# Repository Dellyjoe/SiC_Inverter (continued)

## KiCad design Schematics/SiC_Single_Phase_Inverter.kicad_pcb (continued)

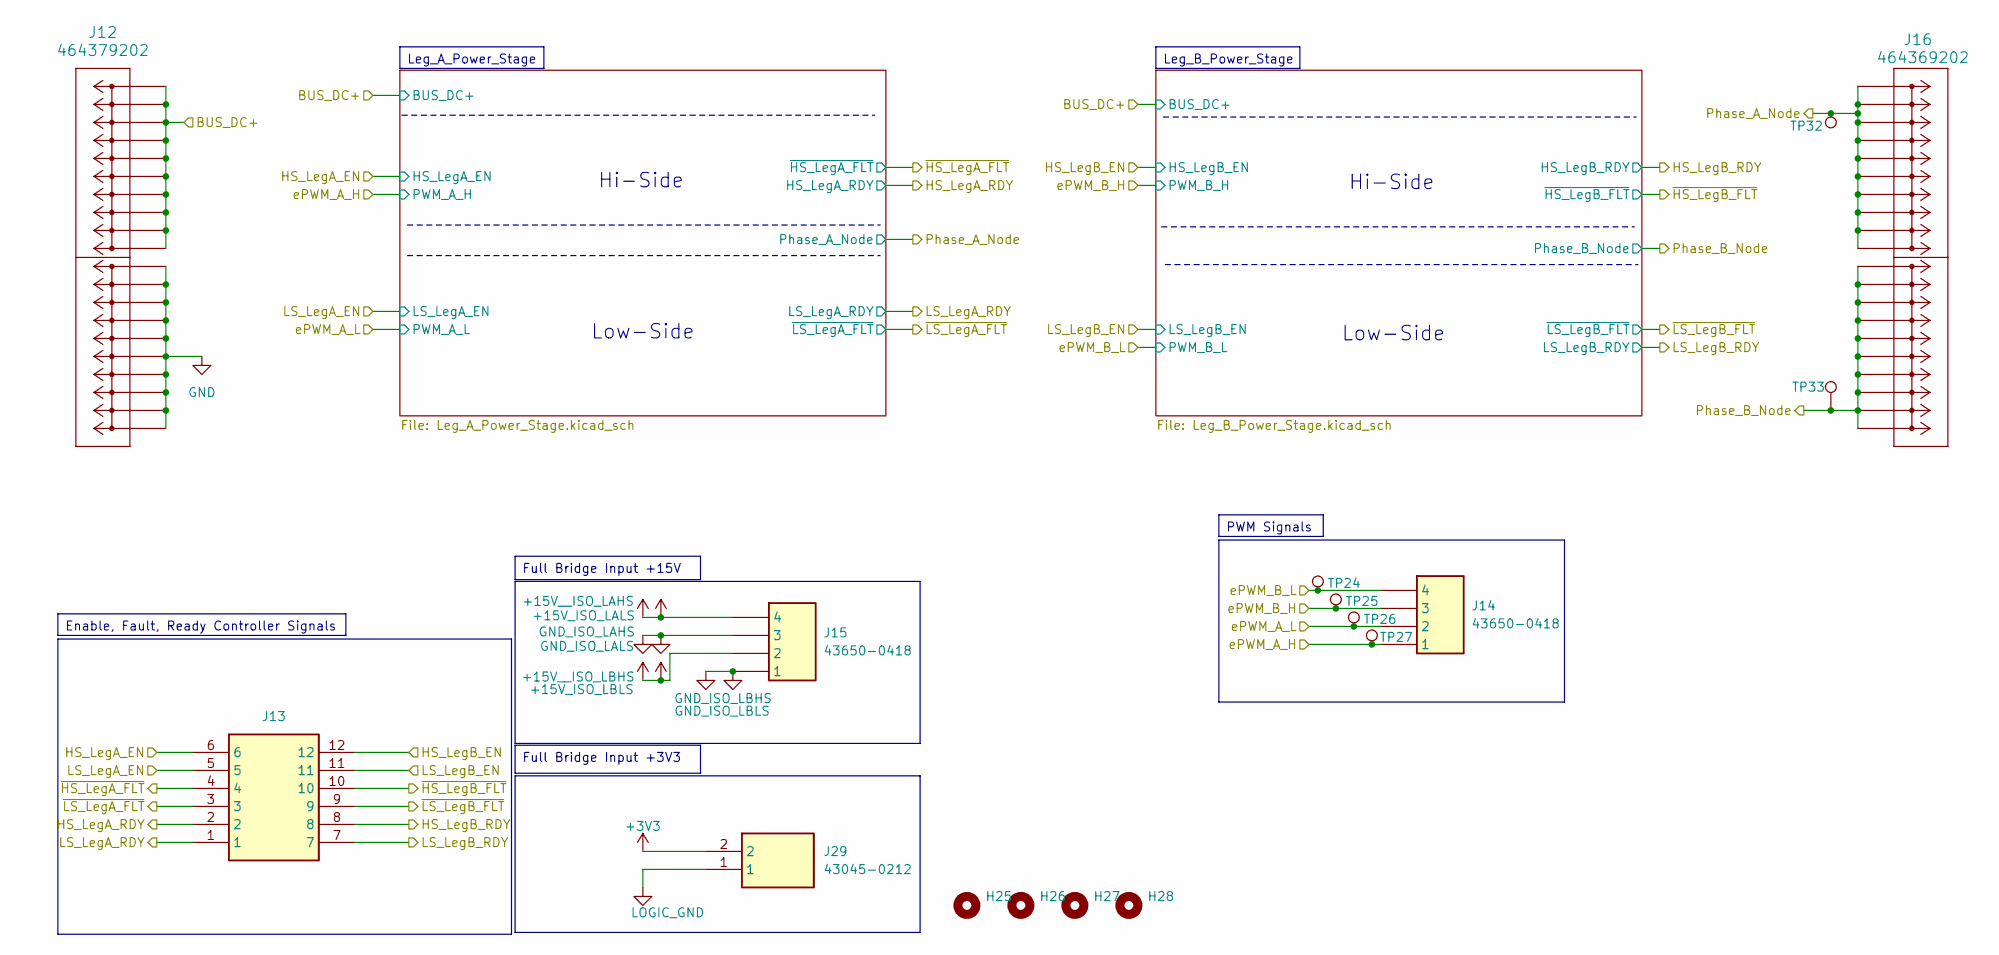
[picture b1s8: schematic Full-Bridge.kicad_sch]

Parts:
H25, H26, H27, H28: MountingHole; MountingHole_2.2mm_M2
J12: 464379202; 46437-900_02
J13: 43045-1212; Mouser Part Number 538-43045-1212
J14, J15: 43650-0418; 436500418; Mouser Part Number 538-43650-0418
J16: 464369202; 46436-900_02
J29: 43045-0212; Mouser Part Number 538-430-45-0212
TP24, TP25, TP26, TP27, TP32: 5277
TP33: 5281

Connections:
+3V3: J29.2; also elsewhere on the board
+15V_ISO_LALS: J15.4; also elsewhere on the board
+15V_ISO_LBLS: J15.2; also elsewhere on the board
/Con_EN_A_H: J13.6; also elsewhere on the board
/Con_EN_A_L: J13.5; also elsewhere on the board
/Con_EN_B_H: J13.12; also elsewhere on the board
/Con_EN_B_L: J13.11; also elsewhere on the board
/Con_FLT_A_H: J13.4; also elsewhere on the board
/Con_FLT_A_L: J13.3; also elsewhere on the board
/Con_FLT_B_H: J13.10; also elsewhere on the board
/Con_FLT_B_L: J13.9; also elsewhere on the board
/Con_PWM_A_H: J14.1, TP27.1 (1_1); also elsewhere on the board
/Con_PWM_A_L: J14.2, TP26.1 (1_1); also elsewhere on the board
/Con_PWM_B_H: J14.3, TP25.1 (1_1); also elsewhere on the board
/Con_PWM_B_L: J14.4, TP24.1 (1_1); also elsewhere on the board
/Con_RDY_A_H: J13.2; also elsewhere on the board
/Con_RDY_A_L: J13.1; also elsewhere on the board
/Con_RDY_B_H: J13.8; also elsewhere on the board
/Con_RDY_B_L: J13.7; also elsewhere on the board
/DC_Link_Caps/BUS_DC+: J12.P2_1, J12.P2_2, J12.P2_3, J12.P2_4, J12.P2_5, J12.P2_6, J12.P2_7, J12.P2_8, J12.P2_9, J12.P2_10; also elsewhere on the board
GND: J12.P1_1, J12.P1_2, J12.P1_3, J12.P1_4, J12.P1_5, J12.P1_6, J12.P1_7, J12.P1_8, J12.P1_9, J12.P1_10; also elsewhere on the board
GND_ISO_LAHS: J15.3, J16.P1_1, J16.P1_2, J16.P1_3, J16.P1_4, J16.P1_5, J16.P1_6, J16.P1_7, J16.P1_8, J16.P1_9, J16.P1_10, TP32.1 (1_1); also elsewhere on the board
GND_ISO_LBHS: J15.1, J16.P2_1, J16.P2_2, J16.P2_3, J16.P2_4, J16.P2_5, J16.P2_6, J16.P2_7, J16.P2_8, J16.P2_9, J16.P2_10, TP33.1 (1_1); also elsewhere on the board
LOGIC_GND: J29.1; also elsewhere on the board

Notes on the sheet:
Hi-Side
Low-Side
PWM Signals
Full Bridge Input +15V
Full Bridge Input +3V3
Leg_B_Power_Stage
Enable, Fault, Ready Controller Signals
Leg_A_Power_Stage

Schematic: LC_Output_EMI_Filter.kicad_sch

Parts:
C53: 6.8 uF; C4AF9BW4680T3FK; Manufacturer_Part_Number C4AF9BW4680T3FK
H29, H30, H31, H32: MountingHole; MountingHole_2.2mm_M2
J3: 23AH8786-Red
J4: 23AH8785-Black
J17: 464379202; 46437-900_02
L3, L4: 470 uH; 1140471KRC; Mouser Part Number 542-1140-471K-RC
R33: 6; CW005100R0JE12HE
TP3: 5277
TP4: 5281

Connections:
/Phase_A_Output: C53.1, C53.3, J3.1 (1_1), L3.2, R33.1, TP3.1 (1_1)
/Phase_B_Output: C53.2, C53.4, J4.1 (1_1), L4.2, R33.2, TP4.1 (1_1)
GND_ISO_LAHS: J17.P2_1, J17.P2_2, J17.P2_3, J17.P2_4, J17.P2_5, J17.P2_6, J17.P2_7, J17.P2_8, J17.P2_9, J17.P2_10, L3.1; also elsewhere on the board
GND_ISO_LBHS: J17.P1_1, J17.P1_2, J17.P1_3, J17.P1_4, J17.P1_5, J17.P1_6, J17.P1_7, J17.P1_8, J17.P1_9, J17.P1_10, L4.1; also elsewhere on the board

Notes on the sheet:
1. A floating 120 Vrms line‑to‑line output is a valid 120 V AC source Most people think "120 V" means "120 V from hot to neutral," but electrically: • Appliances only care about the voltage across their two input terminals. • They do not require one of those terminals to be neutral or earth‑referen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
LCL AC Output Filter

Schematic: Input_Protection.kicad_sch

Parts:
C66: 0.1 uF; C_0805_2012Metric_Pad1.18x1.45mm_HandSolder
D6: P6KE500A-HF; D_DO-15_P12.70mm_Horizontal
D7: BZX84C15-7-F; SOT-23-3
F1: 0031.8322
H1, H2, H3, H4: MountingHole; MountingHole_2.2mm_M2
J1: 23AH8786-Red
J2: 23AH8785-Black
J23: 464369202; 46436-900_02
J24: 43650-0418; 436500418; Mouser Part Number 538-43650-0418
Q8: STB10NK60ZT4; TO-263-2
R44, R45: 499 K; R_1206_3216Metric_Pad1.30x1.75mm_HandSolder
R46: 47; R_1206_3216Metric_Pad1.30x1.75mm_HandSolder
R47: 100 K; R_1206_3216Metric_Pad1.30x1.75mm_HandSolder
TP1, TP67, TP69: 5277
TP2, TP68: 5281

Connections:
+VIN: F1.1, J1.1 (1_1), TP1.1 (1_1)
-VIN: J2.1 (1_1), Q8.2, TP2.1 (1_1)
/Con_Pro_Gate_node_output: C66.2, D7.1 (K), J24.4, R45.2, R46.2, R47.2, TP67.1 (1_1); also elsewhere on the board
/EMI_Input_Filter/+VIN_EMI: D6.1 (K), F1.2, J23.P1_1, J23.P1_2, J23.P1_3, J23.P1_4, J23.P1_5, J23.P1_6, J23.P1_7, J23.P1_8, J23.P1_9, J23.P1_10, J24.2, J24.3, R44.1, TP69.1 (1_1); also elsewhere on the board
GND: C66.1, D6.2 (A), D7.2 (A), J23.P2_1, J23.P2_2, J23.P2_3, J23.P2_4, J23.P2_5, J23.P2_6, J23.P2_7, J23.P2_8, J23.P2_9, J23.P2_10, J24.1, Q8.3, R47.1, TP68.1 (1_1); also elsewhere on the board
unnamed: Q8.1 (G), R46.1
unnamed: R44.2, R45.1

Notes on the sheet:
This stage protects the inverter from incorrect wiring, overcurrent faults, and high‑energy transients on the DC input. The protection chain consists of a series fuse on the positive rail, a low‑side N‑MOSFET used as an ideal‑diode reverse‑polarity protector, and a high‑voltage TVS diode across the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
Input Protection Overview
Protected Voltage and GPIO to Power Board
Input Protection: Fuse, Reverse-polarity, OC, Protection

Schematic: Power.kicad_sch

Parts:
H9, H10, H11, H12: MountingHole; MountingHole_2.2mm_M2
J25, J26, J27: 43650-0418; 436500418; Mouser Part Number 538-43650-0418
J30: 43045-0212; Mouser Part Number 538-430-45-0212
PS1, PS2: IRM-03-15
TP70, TP73, TP75: 5281
TP71, TP72, TP74: 5277
U5: TR05S3V3

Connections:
+3V3: J26.2, J30.2, TP71.1 (1_1), U5.3 (+VOUT); also elsewhere on the board
+15V_ISO_LALS: J27.4, PS1.16 (+VO), TP72.1 (1_1), U5.1 (+VIN); also elsewhere on the board
+15V_ISO_LBLS: J27.2, PS2.16 (+VO), TP74.1 (1_1); also elsewhere on the board
/Con_Pro_Gate_node_output: J25.4, J26.4; also elsewhere on the board
/EMI_Input_Filter/+VIN_EMI: J25.2, J25.3, PS1.1 (AC/L), PS2.1 (AC/L); also elsewhere on the board
GND: J25.1, J26.3, PS1.3 (AC/N), PS2.3 (AC/N); also elsewhere on the board
GND_ISO_LAHS: J27.3, PS1.14 (-VO), TP73.1 (1_1); also elsewhere on the board
GND_ISO_LBHS: J27.1, PS2.14 (-VO), TP75.1 (1_1); also elsewhere on the board
LOGIC_GND: J26.1, J30.1, TP70.1 (1_1), U5.2 (GND); also elsewhere on the board

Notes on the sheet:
Isolated Leg B Half Bridge: 15V Output
Isolated Leg A Half Bridge: 15V Output
Input Voltage From Protection Circuit
Power Supply +3V3 logic Power
Output to Full Bridge +3V3

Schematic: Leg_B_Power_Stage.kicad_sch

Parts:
C35, C36: 15 uF; C_1206_3216Metric_Pad1.33x1.80mm_HandSolder
C37, C38, C44, C47, C48, C51: 0.1 uF; C_0805_2012Metric_Pad1.18x1.45mm_HandSolder
C39, C40, C45, C52: 1 uF; C_1206_3216Metric_Pad1.33x1.80mm_HandSolder
C41, C42, C43, C46, C49, C50: 100 pF; C_0603_1608Metric_Pad1.08x0.95mm_HandSolder
D4, D5: BZX84C20-7-F; SOT-23-3
Q4, Q5: C3M0025065K
R19, R20: 100 K; R_1206_3216Metric_Pad1.30x1.75mm_HandSolder
R21, R22, R23, R24: 10; R_1206_3216Metric_Pad1.30x1.75mm_HandSolder
R25, R27, R28, R30, R31, R32: 5 K; R_1206_3216Metric_Pad1.30x1.75mm_HandSolder
R26, R29: 100; R_1206_3216Metric_Pad1.30x1.75mm_HandSolder
TP36, TP37: 5277
U3, U4: UCC21710QDWRQ1; Mouser Part Number 595-UCC21710QDWRQ1

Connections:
+3V3: C44.1, C45.1, C51.1, C52.1, R25.1, R27.1, R28.1, R30.1, R31.1, R32.1, U3.15 (VCC), U4.15 (VCC); also elsewhere on the board
+15V_ISO_LBLS: C35.1, C36.1, C37.1, C38.1, C39.1, C40.1, U3.5 (VDD), U4.5 (VDD); also elsewhere on the board
/Con_EN_B_H: C50.1, R27.2, U4.14 (~RST/EN); also elsewhere on the board
/Con_EN_B_L: C43.1, R25.2, U3.14 (~RST/EN); also elsewhere on the board
/Con_FLT_B_H: C49.1, R30.2, U4.13 (~FLT); also elsewhere on the board
/Con_FLT_B_L: C42.1, R28.2, U3.13 (~FLT); also elsewhere on the board
/Con_PWM_B_H: R29.2; also elsewhere on the board
/Con_PWM_B_L: R26.2; also elsewhere on the board
/Con_RDY_B_H: C46.1, R32.2, U4.12 (RDY); also elsewhere on the board
/Con_RDY_B_L: C41.1, R31.2, U3.12 (RDY); also elsewhere on the board
/DC_Link_Caps/BUS_DC+: Q4.1; also elsewhere on the board
/Full-Bridge/Leg_B_Power_Stage/LegB_HS_Gate: D4.1 (K), Q4.4, R19.1, R21.2, R22.2, TP36.1 (1_1), U4.7 (CLMPI)
/Full-Bridge/Leg_B_Power_Stage/LegB_HS_OUTH: R21.1, U4.4 (OUTH)
/Full-Bridge/Leg_B_Power_Stage/LegB_HS_OUTL: R22.1, U4.6 (OUTL)
/Full-Bridge/Leg_B_Power_Stage/LegB_LS_Gate: D5.1 (K), Q5.4, R20.1, R23.2, R24.2, TP37.1 (1_1), U3.7 (CLMPI)
/Full-Bridge/Leg_B_Power_Stage/LegB_LS_OUTH: R23.1, U3.4 (OUTH)
/Full-Bridge/Leg_B_Power_Stage/LegB_LS_OUTL: R24.1, U3.6 (OUTL)
GND: C36.2, C38.2, C40.2, D5.2 (A), Q5.2, Q5.3, R20.2, U3.1 (AIN), U3.2 (OC), U3.3 (COM); also elsewhere on the board
GND_ISO_LBHS: C35.2, C37.2, C39.2, D4.2 (A), Q4.2, Q4.3, Q5.1, R19.2, U3.8 (VEE), U4.1 (AIN), U4.2 (OC), U4.3 (COM), U4.8 (VEE); also elsewhere on the board
LOGIC_GND: C41.2, C42.2, C43.2, C44.2, C45.2, C46.2, C47.2, C48.2, C49.2, C50.2, C51.2, C52.2, U3.9 (GND), U3.11 (IN-), U4.9 (GND), U4.11 (IN-); also elsewhere on the board
unnamed: C47.1, R26.1, U3.10 (IN+)
unnamed: C48.1, R29.1, U4.10 (IN+)

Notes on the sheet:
Pick out 15 uF, 0.1 uF , and 1 uF cap and fill out footprint Before moving on to the Low Side for Leg A
Leg BH Bypass Caps
Leg B
Need a Isoulated DC-DC Converter for this. THe 15V output will be +15V_ISO_LALS and GND_ISO_LALS
R0ff
High Side
Ron
Leg BL Bypass Caps
Low Side
Ceramic
Need a Isoulated DC-DC Converter for this. THe 15V output will be +15V_ISO_LAHS and GND_ISO_LAHS

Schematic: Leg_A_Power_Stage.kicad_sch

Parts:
C17, C18: 15 uF; C_1206_3216Metric_Pad1.33x1.80mm_HandSolder
C19, C20, C26, C29, C30, C33: 0.1 uF; C_0805_2012Metric_Pad1.18x1.45mm_HandSolder
C21, C22, C27, C34: 1 uF; C_1206_3216Metric_Pad1.33x1.80mm_HandSolder
C23, C24, C25, C28, C31, C32: 100 pF; C_0603_1608Metric_Pad1.08x0.95mm_HandSolder
D2, D3: BZX84C20-7-F; SOT-23-3
Q2, Q3: C3M0025065K
R5, R6: 100 K; R_1206_3216Metric_Pad1.30x1.75mm_HandSolder
R7, R8, R9, R10: 10; R_1206_3216Metric_Pad1.30x1.75mm_HandSolder
R11, R13, R14, R16, R17, R18: 5 K; R_1206_3216Metric_Pad1.30x1.75mm_HandSolder
R12, R15: 100; R_1206_3216Metric_Pad1.30x1.75mm_HandSolder
TP34, TP35: 5277
U1, U2: UCC21710QDWRQ1; Mouser Part Number 595-UCC21710QDWRQ1

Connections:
+3V3: C26.1, C27.1, C33.1, C34.1, R11.1, R13.1, R14.1, R16.1, R17.1, R18.1, U1.15 (VCC), U2.15 (VCC); also elsewhere on the board
+15V_ISO_LALS: C17.1, C18.1, C19.1, C20.1, C21.1, C22.1, U1.5 (VDD), U2.5 (VDD); also elsewhere on the board
/Con_EN_A_H: C32.1, R13.2, U2.14 (~RST/EN); also elsewhere on the board
/Con_EN_A_L: C25.1, R11.2, U1.14 (~RST/EN); also elsewhere on the board
/Con_FLT_A_H: C31.1, R16.2, U2.13 (~FLT); also elsewhere on the board
/Con_FLT_A_L: C24.1, R14.2, U1.13 (~FLT); also elsewhere on the board
/Con_PWM_A_H: R15.2; also elsewhere on the board
/Con_PWM_A_L: R12.2; also elsewhere on the board
/Con_RDY_A_H: C28.1, R18.2, U2.12 (RDY); also elsewhere on the board
/Con_RDY_A_L: C23.1, R17.2, U1.12 (RDY); also elsewhere on the board
/DC_Link_Caps/BUS_DC+: Q2.1; also elsewhere on the board
/Full-Bridge/Leg_A_Power_Stage/LegA_HS_Gate: D2.1 (K), Q2.4, R5.1, R7.2, R8.2, TP34.1 (1_1), U2.7 (CLMPI)
/Full-Bridge/Leg_A_Power_Stage/LegA_HS_OUTH: R7.1, U2.4 (OUTH)
/Full-Bridge/Leg_A_Power_Stage/LegA_HS_OUTL: R8.1, U2.6 (OUTL)
/Full-Bridge/Leg_A_Power_Stage/LegA_LS_Gate: D3.1 (K), Q3.4, R6.1, R9.2, R10.2, TP35.1 (1_1), U1.7 (CLMPI)
/Full-Bridge/Leg_A_Power_Stage/LegA_LS_OUTH: R9.1, U1.4 (OUTH)
/Full-Bridge/Leg_A_Power_Stage/LegA_LS_OUTL: R10.1, U1.6 (OUTL)
GND: C18.2, C20.2, C22.2, D3.2 (A), Q3.2, Q3.3, R6.2, U1.1 (AIN), U1.2 (OC), U1.3 (COM); also elsewhere on the board
GND_ISO_LAHS: C17.2, C19.2, C21.2, D2.2 (A), Q2.2, Q2.3, Q3.1, R5.2, U1.8 (VEE), U2.1 (AIN), U2.2 (OC), U2.3 (COM), U2.8 (VEE); also elsewhere on the board
LOGIC_GND: C23.2, C24.2, C25.2, C26.2, C27.2, C28.2, C29.2, C30.2, C31.2, C32.2, C33.2, C34.2, U1.9 (GND), U1.11 (IN-), U2.9 (GND), U2.11 (IN-); also elsewhere on the board
unnamed: C29.1, R12.1, U1.10 (IN+)
unnamed: C30.1, R15.1, U2.10 (IN+)

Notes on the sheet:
Ron
R0ff
Low Side
Ceramic
High Side
Leg AL Bypass Caps
Leg AH Bypass Caps
Leg A

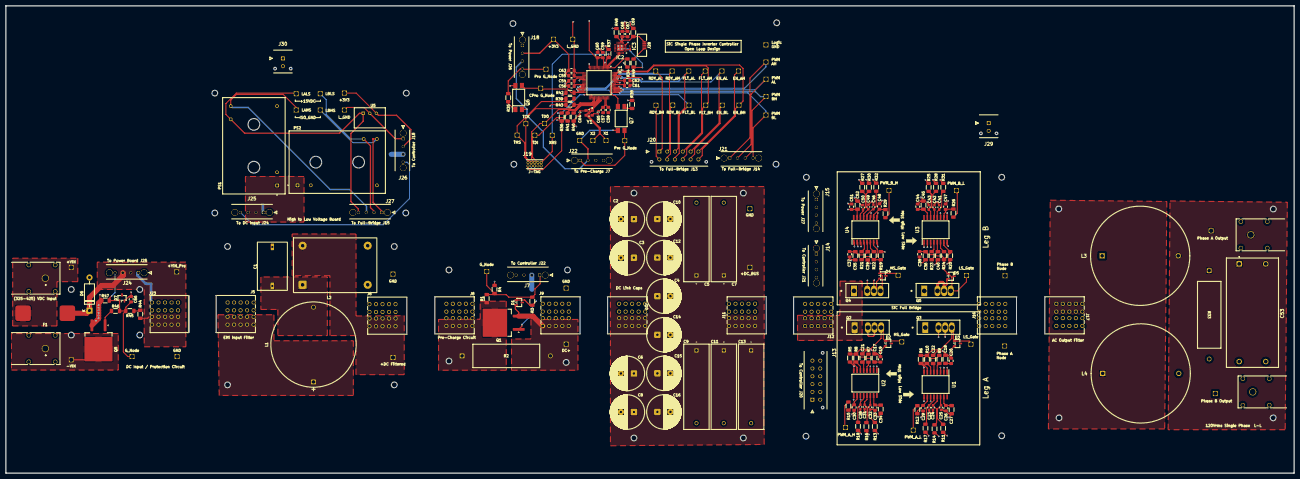
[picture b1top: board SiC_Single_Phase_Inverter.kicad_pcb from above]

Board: 2 copper layers, 494.6 x 179.4 mm, 271 parts (0 on the bottom side), 74 nets.

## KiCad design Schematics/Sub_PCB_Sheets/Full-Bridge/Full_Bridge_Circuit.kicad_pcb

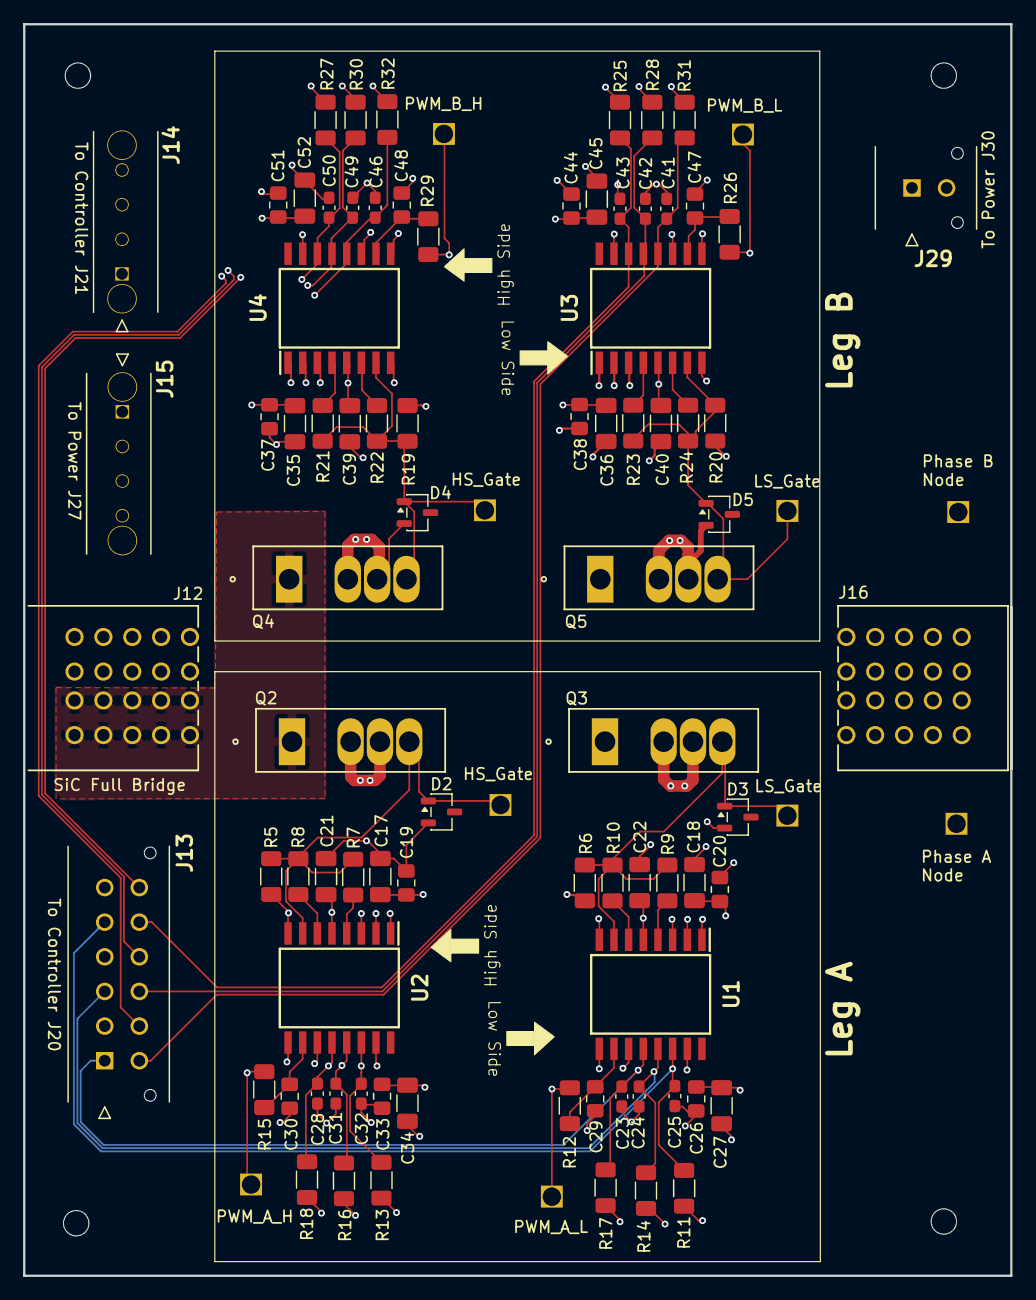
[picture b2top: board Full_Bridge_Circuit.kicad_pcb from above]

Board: 4 copper layers, 85.5 x 108.4 mm, 96 parts (0 on the bottom side), 40 nets.

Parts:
C17, C18, C35, C36: 15 uF; C_1206_3216Metric_Pad1.33x1.80mm_HandSolder
C19, C20, C26, C29, C30, C33, C37, C38, C44, C47, C48, C51: 0.1 uF; C_0805_2012Metric_Pad1.18x1.45mm_HandSolder
C21, C22, C27, C34, C39, C40, C45, C52: 1 uF; C_1206_3216Metric_Pad1.33x1.80mm_HandSolder
C23, C24, C25, C28, C31, C32, C41, C42, C43, C46, C49, C50: 100 pF; C_0603_1608Metric_Pad1.08x0.95mm_HandSolder
D2, D3, D4, D5: BZX84C20-7-F; SOT-23-3
H25, H26, H27, H28: MountingHole; MountingHole_2.2mm_M2
J12: 464379202; 46437-900_02
J13: 43045-1212
J14, J15: 43650-0418; 436500418
J16: 464369202; 46436-900_02
J29: 43045-0212
Q2, Q3, Q4, Q5: TO-247-4_CRW; C3M0025065K
R5, R6, R19, R20: 100 K; R_1206_3216Metric_Pad1.30x1.75mm_HandSolder
R7, R8, R9, R10, R21, R22, R23, R24: 10; R_1206_3216Metric_Pad1.30x1.75mm_HandSolder
R11, R13, R14, R16, R17, R18, R25, R27, R28, R30, R31, R32: 5 K; R_1206_3216Metric_Pad1.30x1.75mm_HandSolder
R12, R15, R26, R29: 100; R_1206_3216Metric_Pad1.30x1.75mm_HandSolder
TP24, TP25, TP26, TP27, TP32, TP34, TP35, TP36, TP37: 5277
TP33: 5281
U1, U2, U3, U4: SOIC127P1030X265-16N; UCC21710QDWRQ1

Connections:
+3V3: C26.1, C27.1, C33.1, C34.1, C44.1, C45.1, C51.1, C52.1, J29.2, R11.1, R13.1, R14.1, R16.1, R17.1, R18.1, R25.1, R27.1, R28.1, R30.1, R31.1, R32.1, U1.15 (VCC), U2.15 (VCC), U3.15 (VCC), U4.15 (VCC)
+15V_ISO_LALS: C17.1, C18.1, C19.1, C20.1, C21.1, C22.1, J15.4, U1.5 (VDD), U2.5 (VDD)
+15V_ISO_LBLS: C35.1, C36.1, C37.1, C38.1, C39.1, C40.1, J15.2, U3.5 (VDD), U4.5 (VDD)
/Con_EN_A_H: C32.1, J13.6, R13.2, U2.14 (~RST/EN)
/Con_EN_A_L: C25.1, J13.5, R11.2, U1.14 (~RST/EN)
/Con_EN_B_H: C50.1, J13.12, R27.2, U4.14 (~RST/EN)
/Con_EN_B_L: C43.1, J13.11, R25.2, U3.14 (~RST/EN)
/Con_FLT_A_H: C31.1, J13.4, R16.2, U2.13 (~FLT)
/Con_FLT_A_L: C24.1, J13.3, R14.2, U1.13 (~FLT)
/Con_FLT_B_H: C49.1, J13.10, R30.2, U4.13 (~FLT)
/Con_FLT_B_L: C42.1, J13.9, R28.2, U3.13 (~FLT)
/Con_PWM_A_H: J14.1, R15.2, TP27.1 (1_1)
/Con_PWM_A_L: J14.2, R12.2, TP26.1 (1_1)
/Con_PWM_B_H: J14.3, R29.2, TP25.1 (1_1)
/Con_PWM_B_L: J14.4, R26.2, TP24.1 (1_1)
/Con_RDY_A_H: C28.1, J13.2, R18.2, U2.12 (RDY)
/Con_RDY_A_L: C23.1, J13.1, R17.2, U1.12 (RDY)
/Con_RDY_B_H: C46.1, J13.8, R32.2, U4.12 (RDY)
/Con_RDY_B_L: C41.1, J13.7, R31.2, U3.12 (RDY)
/DC_Link_Caps/BUS_DC+: J12.P2_1, J12.P2_2, J12.P2_3, J12.P2_4, J12.P2_5, J12.P2_6, J12.P2_7, J12.P2_8, J12.P2_9, J12.P2_10, Q2.1, Q4.1
/Full-Bridge/Leg_A_Power_Stage/LegA_HS_Gate: D2.1 (K), Q2.4, R5.1, R7.2, R8.2, TP34.1 (1_1), U2.7 (CLMPI)
/Full-Bridge/Leg_A_Power_Stage/LegA_HS_OUTH: R7.1, U2.4 (OUTH)
/Full-Bridge/Leg_A_Power_Stage/LegA_HS_OUTL: R8.1, U2.6 (OUTL)
/Full-Bridge/Leg_A_Power_Stage/LegA_LS_Gate: D3.1 (K), Q3.4, R6.1, R9.2, R10.2, TP35.1 (1_1), U1.7 (CLMPI)
/Full-Bridge/Leg_A_Power_Stage/LegA_LS_OUTH: R9.1, U1.4 (OUTH)
/Full-Bridge/Leg_A_Power_Stage/LegA_LS_OUTL: R10.1, U1.6 (OUTL)
/Full-Bridge/Leg_B_Power_Stage/LegB_HS_Gate: D4.1 (K), Q4.4, R19.1, R21.2, R22.2, TP36.1 (1_1), U4.7 (CLMPI)
/Full-Bridge/Leg_B_Power_Stage/LegB_HS_OUTH: R21.1, U4.4 (OUTH)
/Full-Bridge/Leg_B_Power_Stage/LegB_HS_OUTL: R22.1, U4.6 (OUTL)
/Full-Bridge/Leg_B_Power_Stage/LegB_LS_Gate: D5.1 (K), Q5.4, R20.1, R23.2, R24.2, TP37.1 (1_1), U3.7 (CLMPI)
/Full-Bridge/Leg_B_Power_Stage/LegB_LS_OUTH: R23.1, U3.4 (OUTH)
/Full-Bridge/Leg_B_Power_Stage/LegB_LS_OUTL: R24.1, U3.6 (OUTL)
GND: C18.2, C20.2, C22.2, C36.2, C38.2, C40.2, D3.2 (A), D5.2 (A), J12.P1_1, J12.P1_2, J12.P1_3, J12.P1_4, J12.P1_5, J12.P1_6, J12.P1_7, J12.P1_8, J12.P1_9, J12.P1_10, Q3.2, Q3.3, Q5.2, Q5.3, R6.2, R20.2, U1.1 (AIN), U1.2 (OC), U1.3 (COM), U3.1 (AIN), U3.2 (OC), U3.3 (COM)
GND_ISO_LAHS: C17.2, C19.2, C21.2, D2.2 (A), J15.3, J16.P1_1, J16.P1_2, J16.P1_3, J16.P1_4, J16.P1_5, J16.P1_6, J16.P1_7, J16.P1_8, J16.P1_9, J16.P1_10, Q2.2, Q2.3, Q3.1, R5.2, TP32.1 (1_1), U1.8 (VEE), U2.1 (AIN), U2.2 (OC), U2.3 (COM), U2.8 (VEE)
GND_ISO_LBHS: C35.2, C37.2, C39.2, D4.2 (A), J15.1, J16.P2_1, J16.P2_2, J16.P2_3, J16.P2_4, J16.P2_5, J16.P2_6, J16.P2_7, J16.P2_8, J16.P2_9, J16.P2_10, Q4.2, Q4.3, Q5.1, R19.2, TP33.1 (1_1), U3.8 (VEE), U4.1 (AIN), U4.2 (OC), U4.3 (COM), U4.8 (VEE)
LOGIC_GND: C23.2, C24.2, C25.2, C26.2, C27.2, C28.2, C29.2, C30.2, C31.2, C32.2, C33.2, C34.2, C41.2, C42.2, C43.2, C44.2, C45.2, C46.2, C47.2, C48.2, C49.2, C50.2, C51.2, C52.2, J29.1, U1.9 (GND), U1.11 (IN-), U2.9 (GND), U2.11 (IN-), U3.9 (GND), U3.11 (IN-), U4.9 (GND), U4.11 (IN-)
unnamed: C29.1, R12.1, U1.10 (IN+)
unnamed: C30.1, R15.1, U2.10 (IN+)
unnamed: C47.1, R26.1, U3.10 (IN+)
unnamed: C48.1, R29.1, U4.10 (IN+)

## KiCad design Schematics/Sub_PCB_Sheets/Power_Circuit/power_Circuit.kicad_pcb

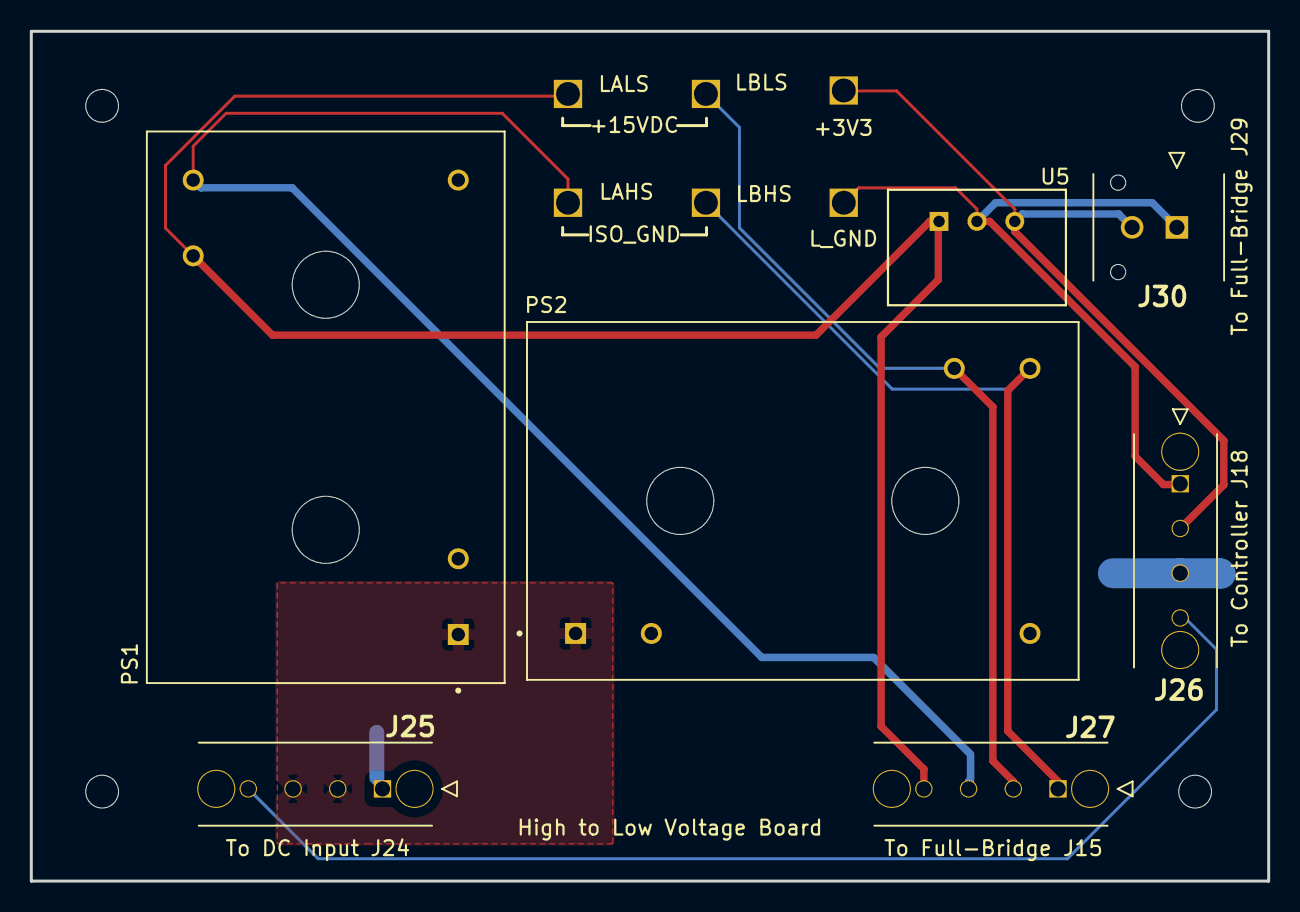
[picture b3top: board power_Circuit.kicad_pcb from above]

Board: 2 copper layers, 83.0 x 57.0 mm, 17 parts (0 on the bottom side), 9 nets.

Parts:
H9, H10, H11, H12: MountingHole; MountingHole_2.2mm_M2
J25, J26, J27: 43650-0418; 436500418
J30: 43045-0212
PS1, PS2: IRM-03-15
TP70, TP73, TP75: 5281
TP71, TP72, TP74: 5277
U5: TR05S3V3

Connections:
+3V3: J26.2, J30.2, TP71.1 (1_1), U5.3 (+VOUT)
+15V_ISO_LALS: J27.4, PS1.16 (+VO), TP72.1 (1_1), U5.1 (+VIN)
+15V_ISO_LBLS: J27.2, PS2.16 (+VO), TP74.1 (1_1)
/Con_Pro_Gate_node_output: J25.4, J26.4
/EMI_Input_Filter/+VIN_EMI: J25.2, J25.3, PS1.1 (AC/L), PS2.1 (AC/L)
GND: J25.1, J26.3, PS1.3 (AC/N), PS2.3 (AC/N)
GND_ISO_LAHS: J27.3, PS1.14 (-VO), TP73.1 (1_1)
GND_ISO_LBHS: J27.1, PS2.14 (-VO), TP75.1 (1_1)
LOGIC_GND: J26.1, J30.1, TP70.1 (1_1), U5.2 (GND)

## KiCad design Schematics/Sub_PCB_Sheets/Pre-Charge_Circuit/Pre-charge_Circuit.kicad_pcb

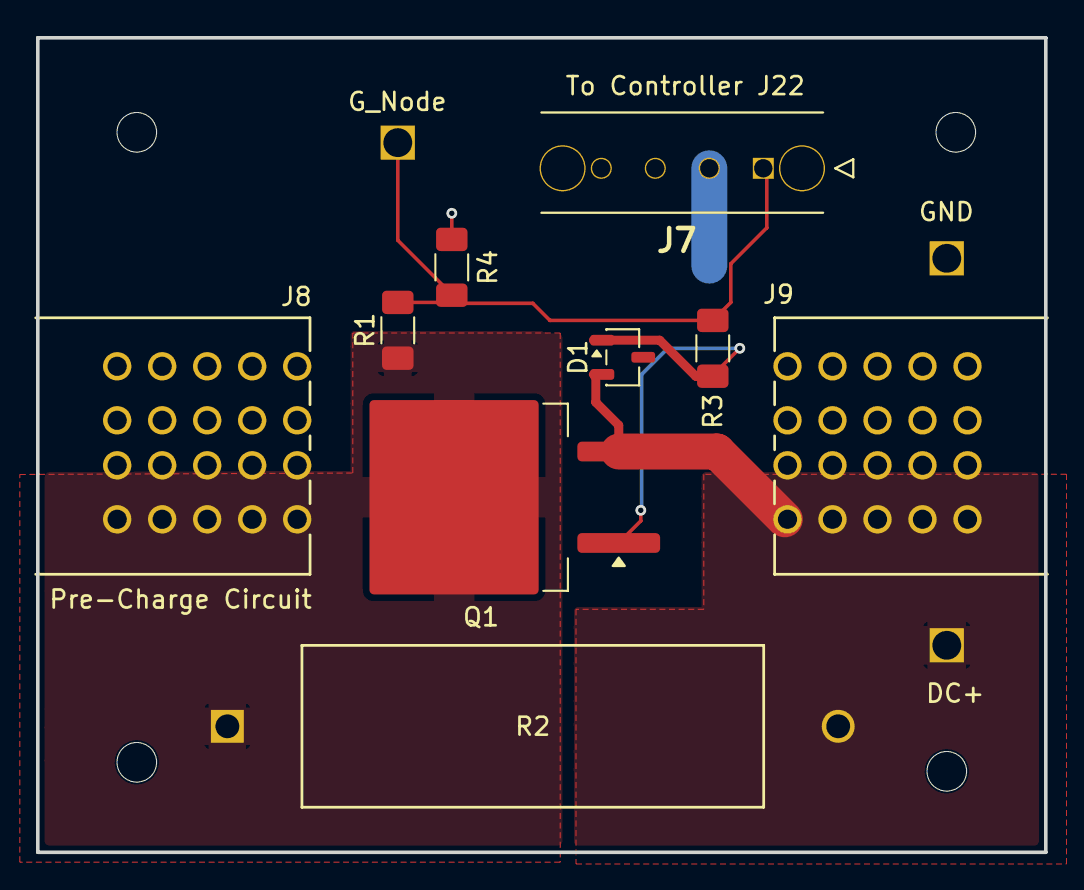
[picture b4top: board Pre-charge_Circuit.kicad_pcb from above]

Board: 2 copper layers, 56.0 x 45.2 mm, 16 parts (0 on the bottom side), 5 nets.

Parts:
D1: BZX84C15-7-F; SOT-23-3
H13, H14, H15, H16: MountingHole; MountingHole_2.2mm_M2
J7: 43650-0418; 436500418
J8: 464379202; 46437-900_02
J9: 464369202; 46436-900_02
Q1: STB10NK60ZT4; TO-263-2
R1: 499 K; R_1206_3216Metric_Pad1.30x1.75mm_HandSolder
R2: CW005100R0JE12HE
R3: 47; R_1206_3216Metric_Pad1.30x1.75mm_HandSolder
R4: 100 K; R_1206_3216Metric_Pad1.30x1.75mm_HandSolder
TP7, TP8: 5277
TP9: 5281

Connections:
/Con_Gate_node_prech: J7.1, R1.2, R3.2, R4.1, TP7.1 (1_1)
/DC_Link_Caps/BUS_DC+: D1.2 (A), J9.P1_1, J9.P1_2, J9.P1_3, J9.P1_4, J9.P1_5, J9.P1_6, J9.P1_7, J9.P1_8, J9.P1_9, J9.P1_10, Q1.3, R2.2, TP8.1 (1_1)
/EMI_Input_Filter/BUS+_Filtered: J8.P2_1, J8.P2_2, J8.P2_3, J8.P2_4, J8.P2_5, J8.P2_6, J8.P2_7, J8.P2_8, J8.P2_9, J8.P2_10, Q1.2, R1.1, R2.1
GND: J7.2, J8.P1_1, J8.P1_2, J8.P1_3, J8.P1_4, J8.P1_5, J8.P1_6, J8.P1_7, J8.P1_8, J8.P1_9, J8.P1_10, J9.P2_1, J9.P2_2, J9.P2_3, J9.P2_4, J9.P2_5, J9.P2_6, J9.P2_7, J9.P2_8, J9.P2_9, J9.P2_10, R4.2, TP9.1 (1_1)
unnamed: D1.1 (K), Q1.1 (G), R3.1

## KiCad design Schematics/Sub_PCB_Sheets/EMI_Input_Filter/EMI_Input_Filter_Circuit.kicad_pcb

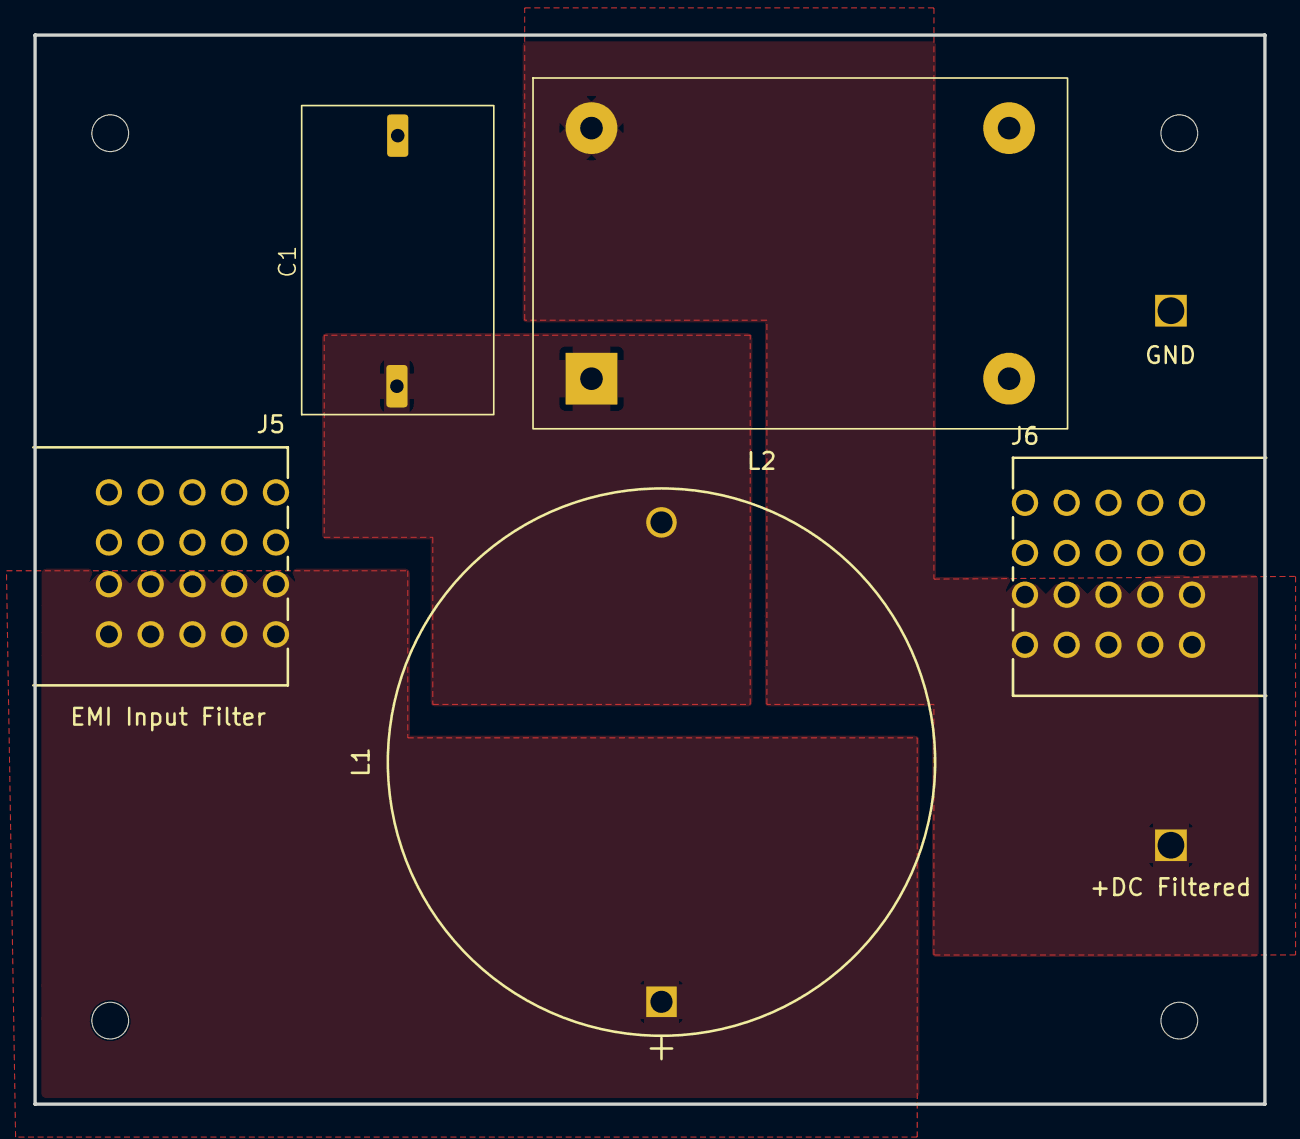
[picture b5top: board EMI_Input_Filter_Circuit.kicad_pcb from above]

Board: 2 copper layers, 73.6 x 64.0 mm, 11 parts (0 on the bottom side), 4 nets, no tracks yet.

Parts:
C1: 1 uF; R71PI410050H6K
H5, H6, H7, H8: MountingHole; MountingHole_2.2mm_M2
J5: 464379202; 46437-900_02
J6: 464369202; 46436-900_02
L1: 47 uH; 2300HT_470
L2: 2.2 mH; 7448258022
TP5: 5277
TP6: 5281

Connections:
/EMI_Input_Filter/+VIN_EMI: J5.P2_1, J5.P2_2, J5.P2_3, J5.P2_4, J5.P2_5, J5.P2_6, J5.P2_7, J5.P2_8, J5.P2_9, J5.P2_10, L1.1
/EMI_Input_Filter/BUS+_Filtered: J6.P1_1, J6.P1_2, J6.P1_3, J6.P1_4, J6.P1_5, J6.P1_6, J6.P1_7, J6.P1_8, J6.P1_9, J6.P1_10, L2.4, TP5.1 (1_1)
/EMI_Input_Filter/BUS+_RAW: C1.1, L1.2, L2.1
GND: C1.2, J5.P1_1, J5.P1_2, J5.P1_3, J5.P1_4, J5.P1_5, J5.P1_6, J5.P1_7, J5.P1_8, J5.P1_9, J5.P1_10, J6.P2_1, J6.P2_2, J6.P2_3, J6.P2_4, J6.P2_5, J6.P2_6, J6.P2_7, J6.P2_8, J6.P2_9, J6.P2_10, L2.2, L2.3, TP6.1 (1_1)

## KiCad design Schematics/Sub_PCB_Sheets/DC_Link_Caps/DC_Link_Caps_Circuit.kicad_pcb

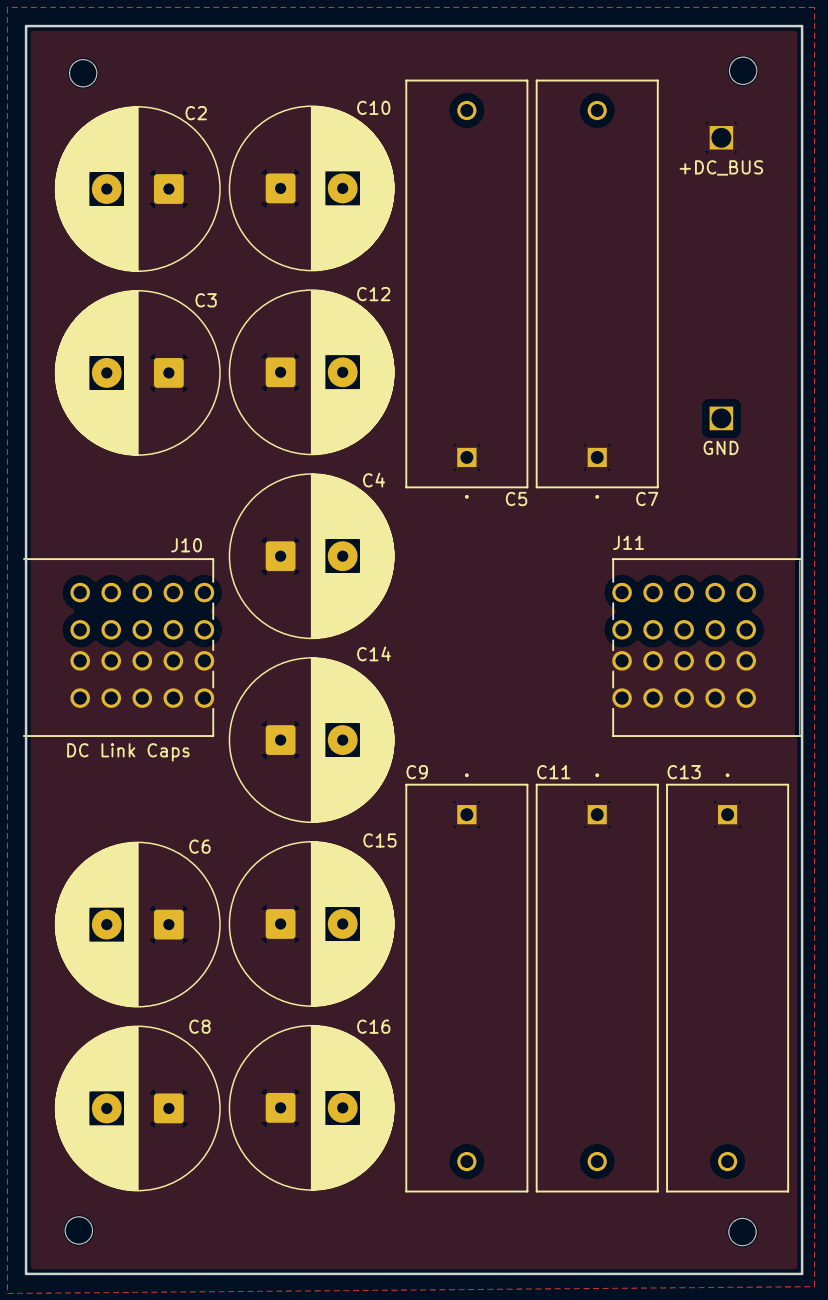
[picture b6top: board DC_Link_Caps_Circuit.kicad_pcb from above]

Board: 2 copper layers, 62.5 x 100.5 mm, 23 parts (0 on the bottom side), 2 nets, no tracks yet.

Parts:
C2, C3, C4, C6, C8, C10, C12, C14, C15, C16: 22 uF; ESH226M500AL4AA
C5, C7, C9, C11, C13: 2 uF; MKP1848C52050JK2
H17, H18, H19, H20: MountingHole; MountingHole_2.2mm_M2
J10: 464379202; 46437-900_02
J11: 464369202; 46436-900_02
TP10: 5281
TP11: 5277

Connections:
/DC_Link_Caps/BUS_DC+: C2.1, C3.1, C4.1, C5.1, C6.1, C7.1, C8.1, C9.1, C10.1, C11.1, C12.1, C13.1, C14.1, C15.1, C16.1, J10.P2_1, J10.P2_2, J10.P2_3, J10.P2_4, J10.P2_5, J10.P2_6, J10.P2_7, J10.P2_8, J10.P2_9, J10.P2_10, J11.P1_1, J11.P1_2, J11.P1_3, J11.P1_4, J11.P1_5, J11.P1_6, J11.P1_7, J11.P1_8, J11.P1_9, J11.P1_10, TP11.1 (1_1)
GND: C2.2, C3.2, C4.2, C5.2, C6.2, C7.2, C8.2, C9.2, C10.2, C11.2, C12.2, C13.2, C14.2, C15.2, C16.2, J10.P1_1, J10.P1_2, J10.P1_3, J10.P1_4, J10.P1_5, J10.P1_6, J10.P1_7, J10.P1_8, J10.P1_9, J10.P1_10, J11.P2_1, J11.P2_2, J11.P2_3, J11.P2_4, J11.P2_5, J11.P2_6, J11.P2_7, J11.P2_8, J11.P2_9, J11.P2_10, TP10.1 (1_1)

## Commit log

2026-02-25 updating read.md
2026-02-25 Adding gitignore
2026-02-25 [SiC Inverter WIP]
    - Deleted backup files
    - changed symbol and footprint lib locations
    - added text discription explaining the DC link sub sheet and emi input
    filter subsheet
    - Added Vin+,- Black and Red connector
2026-02-26 Added 3d models for connectors and caps
2026-02-27 Adding Fuse and TVS Diode to parts list
2026-02-28 Work in progress
    - Added new parts to PCB to check 3d models
    - Added input protection sheet
    - Added TVS, N-Channel MOSFET, Zensor, and resiters to protection
    circuit
    - Added datasheets for new parts
    - Added circuit GND
2026-03-03 [WIP - SIC Inverter]
    - Added 3d models for 3 parts
    - Added 3 new footprints for the 3 added parts
    - Changed footprint 23AH8785 and 86 Black and Red
    - Finished WIP with EMI, Input Protection, and Precharge
    - Added datasheet
2026-03-04 [WIP Full Bridge Leg A High Side]
    - Changed Footprint for Black and Red connectors to THP but no Pin
    number
    - Changed DC Link cap sub sheet to have a cleaner look
    - Change footprint in 1206 reister to head solder pads
    - WIP Full Bridge Leg A High Side
2026-03-04 Added an updated README.MD file
2026-03-05 [LEG A WIP]
    - moved circuits in Leg A HS and LS
    - Completed 90% of HS and LS for LEG A
2026-03-06 Adding 100 pf caps to Leg A circuit, WIP texts
2026-03-06 Copy past Leg A onto Leg B, Changed hames on both High/Low side to match Leg B
2026-03-06 [WIP Full Bridge]
    - Finished Leg B and cleaned up sub sheets Leg A and Leg B
    - Added Hierarchical sheet pins for Leg A,B and Full Bridge
    - Added power schamtic for future use
2026-03-07 Added Footprints for Cap size 15u, 1u, 0.1u and 100p
2026-03-08 Added LCL filter to output EMI Filter
2026-03-08 [WIP SiC Single Phase Inverter
    - Updated README.md
    - Added New Parts for Output filter L,C,R
    - Added datasheets for the new parts
    - Added 3D models for the new parts
    - Added new symbols and footprints for the L,C,R
    - Finished output filter
2026-03-09 [WIP SiC Single Phase Inverter]
    - Added PCB to PCB Male and Female connectors
    - Added symbols, footprints and 3d models for the parts listed above
    - Added Male and Female connectors to input protection and input emi
    subsheets
    - Changed PCB editor to account for two edge cuts/ two sub circuits
2026-03-09 Changing Text to Text Block
2026-03-10 [WIP SiC Single Phase Inverter]
    - Added AC - DC converter for 15V isolated supply
    - Added 2x IRM-05 to the power sub sheet
    - Added 3D part for the IRM-05
2026-03-11 [WIP Single Phase SiC Inverter]
    - Added molex 4 pin pcb connector for +15V power
    - Added 3d model, symbol and footprint
    - Added datasheet for molex connector
    - Added Male and Female pcb - pcb connectors to all sub sheets
2026-03-12 [WIP SiC Single Phase Inverter]
    - Updated README to have a Block Diagram
    - WIP Sub sheets Power, Controller
    - Added the F2800 controller to the project
    - Added the controller to the controller sub sheet
    - Added text for a 15V to 3V3 voltage converter
2026-03-12 Updating README
2026-03-12 Fixing Black Diagram Pic
2026-03-12 Updating Path to Black Digram
2026-03-12 Update README.md
    Updating file path
2026-03-13 [WIP Single Phase Inverter]
    - Changed all Refs within each sub sheet (Stripe)
    - Added 3V3 Power Supply off of 15V iso supply
    - Added footprint, symbol and 3d part
    - updated PCB with new part
2026-03-13 Add files via upload
    Adding a Icon for the SiC Inverter
2026-03-14 WIP: Work on Controller layout, and fixed some sheet text and positions
2026-03-15 [WIP Controller Design]
    - Wired up all 64 Pins on the Controller
    - Added 3d models for connectors and Controller
    - Added data sheets for the newly added parts
    - wired connectors to controller to external PCB Boards
    - Updated Text fields
2026-03-15 [WIP Controller Subsheet]
    - Added USB sub sheet to allow use of a USB connection to controller
    - Added USB parts for USB Circuit
2026-03-16 [Milestone Compelted Controller and USB]
    - Added Test Points
    - Completed USB circuit to Controller
    - Wired up Controller
    - Added Connectors to Power Subsheet and 12pin from cotnroller to Full
    Bridge
    - Added 3d models for USB compoents
2026-03-17 [WIP Input Protection Circuit to Controller]
    - Added Gate node input protection pin to controller
    - Added optocoupler to input protection circuit
    - Added 3d model for PC817.....
    - Updated PCB to test out PCB modularity
2026-03-17 Added Precharge Gate Driver to controller and per charge sub circuit
2026-03-18 WIP PCB, Added Test Points, added icon file
2026-03-19 WIP PCB Design: Finished DC Input / Protection Circuit
2026-03-20 WIP PCB Traceing/Layout
2026-03-21 WIP PCB Design
2026-03-21 Finished PCB Layout and Tracing for Pre-Charge and DC Link Caps
2026-03-21 Adding Mounting holes for DC Link Caps
2026-03-21 Changing units on all Caps to display xF
2026-03-21 Adding Damping Resiter to AC Output Filter and mounting points
2026-03-22 Updating to KiCad 10
2026-03-22 WIP PCB Design Controller
2026-03-23 WIP Controller PCB Layout
2026-03-24 Fixing Full Bridge MOSFET ISO_GND to reference GND or DC-
2026-03-24 Finished Full Bridge Layout
2026-03-24 Adding DC Input project and into PCB for Fab_output
2026-03-24 Milestone Finished WIP PCB for 7 PCBs, Set up folders for each PCB
2026-03-24 Coyping main PCB to sub sheets
2026-03-25 adding AC Output Filter Fab files
2026-03-25 Cleaning up power planes before Fab Output
2026-03-25 Adding Fresh fab output files
2026-03-26 updated controller PCB to 4 layer and finished PCB tracing
2026-03-27 Finishing DC Input PCB circuit and Fab Outputs
2026-03-27 Finishing the DC Link Caps and Fab Outputs
2026-03-27 Finished Input EMI Filter circuit and completed Feb output files
2026-03-27 Power Board PCB completed and generated Feb output files
2026-03-27 Finishing Pre-Charge PCB, added Fab outputs
2026-03-27 Adding two pin connector for 3V3 from power to Full-Bridge
2026-03-27 Added J30 to the Power Board and new Fab output
2026-03-27 WIP Full-Bridge PCB tracing
2026-03-27 Finished Full-Bridge PCB, Fab Outputs
2026-03-27 Adding Zip to project
2026-03-27 Fixing Silkscreen on Full-Bridge
2026-04-07 Adding testing notes for DC Proteciton Circuit
2026-04-07 Adding Hisotry files to gitignore
2026-04-07 Making changes to the Mark Down file.
2026-04-09 Adding testing file for EMI Input Filter
2026-04-11 Adding isoulated dc to dc converter footprint and symbol
